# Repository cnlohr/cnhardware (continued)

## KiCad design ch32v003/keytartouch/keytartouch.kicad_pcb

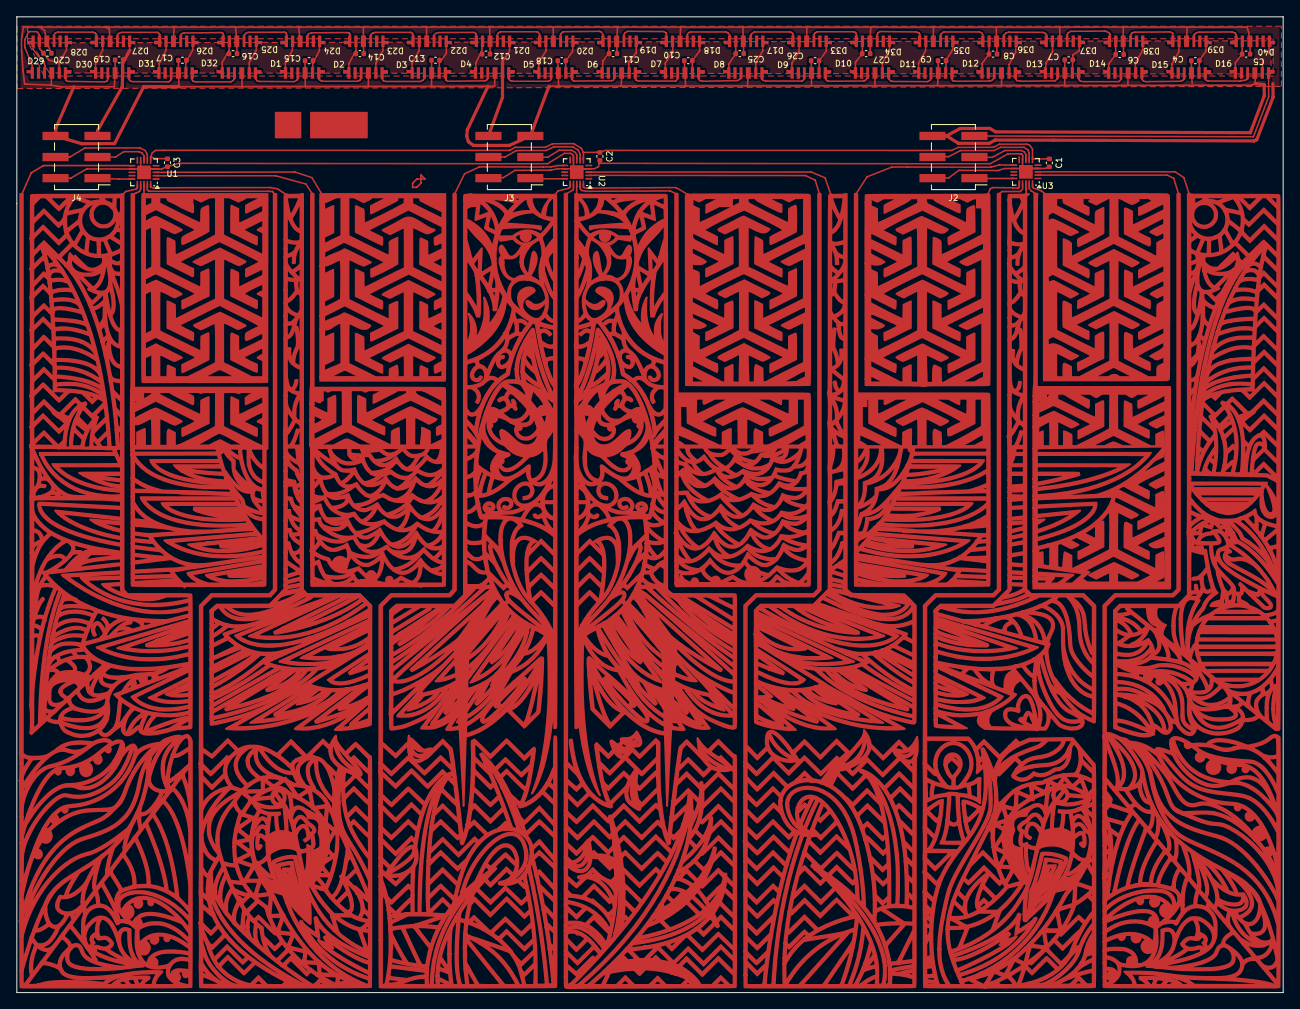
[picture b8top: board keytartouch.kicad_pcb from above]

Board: 2 copper layers, 152.5 x 117.5 mm, 70 parts (0 on the bottom side), 77 nets.

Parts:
C1, C2, C3, C4, C5, C6, C7, C8, C9, C10, C11, C12, C13, C14, C15, C16, C17, C18, C19, C20, C25, C26, C27: .1u; C_0402_1005Metric
D1, D2, D3, D4, D5, D6, D7, D8, D9, D10, D11, D12, D13, D14, D15, D16, D17, D18, D19, D20, D21, D22, D23, D24, D25, D26, D27, D28, D29, D30, D31, D32, D33, D34, D35, D36, D37, D38, D39, D40: SK6805SIDE-FRGBW-BW-P6
J1: CONNS; kelseytop
J2: CC; PinHeader_2x03_P2.54mm_Vertical_SMD
J3: CB; PinHeader_2x03_P2.54mm_Vertical_SMD
J4: CA; PinHeader_2x03_P2.54mm_Vertical_SMD
U1, U2, U3: CH32V003F4U6; QFN-20-1EP_3x3mm_P0.4mm_EP1.65x1.65mm

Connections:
GND: C1.2, C2.2, C3.2, J2.2, J3.2, J4.2, U1.4 (VSS), U1.9 (PC2/SCL/URTS/T1BKIN/AETR/T2CH2/T1ETR), U1.12 (PC5/SCK/T1ETR/T2CH1ETR/SCL/UCK/T1CH3), U1.21 (GND), U2.4 (VSS), U2.9 (PC2/SCL/URTS/T1BKIN/AETR/T2CH2/T1ETR), U2.12 (PC5/SCK/T1ETR/T2CH1ETR/SCL/UCK/T1CH3), U2.21 (GND), U3.4 (VSS), U3.9 (PC2/SCL/URTS/T1BKIN/AETR/T2CH2/T1ETR), U3.12 (PC5/SCK/T1ETR/T2CH1ETR/SCL/UCK/T1CH3), U3.21 (GND)
GND1: C4.2, C5.2, C6.2, C7.2, C8.2, C9.2, C10.2, C11.2, C12.2, C13.2, C14.2, C15.2, C16.2, C17.2, C18.2, C19.2, C20.2, C25.2, C26.2, C27.2, D1.4 (GND), D2.4 (GND), D3.4 (GND), D4.4 (GND), D5.4 (GND), D6.4 (GND), D7.4 (GND), D8.4 (GND), D9.4 (GND), D10.4 (GND), D11.4 (GND), D12.4 (GND), D13.4 (GND), D14.4 (GND), D15.4 (GND), D16.4 (GND), D17.4 (GND), D18.4 (GND), D19.4 (GND), D20.4 (GND), D21.4 (GND), D22.4 (GND), D23.4 (GND), D24.4 (GND), D25.4 (GND), D26.4 (GND), D27.4 (GND), D28.4 (GND), D29.4 (GND), D30.4 (GND), D31.4 (GND), D32.4 (GND), D33.4 (GND), D34.4 (GND), D35.4 (GND), D36.4 (GND), D37.4 (GND), D38.4 (GND), D39.4 (GND), D40.4 (GND), J2.6, J3.5, J4.6
unnamed: D1.6 (DIN), D2.3 (DOUT)
unnamed: D1.3 (DOUT), D32.6 (DIN)
unnamed: D2.6 (DIN), D3.3 (DOUT)
unnamed: D3.6 (DIN), D4.3 (DOUT)
unnamed: D4.6 (DIN), D5.3 (DOUT)
unnamed: D5.6 (DIN), D6.3 (DOUT)
unnamed: D6.6 (DIN), D7.3 (DOUT)
unnamed: D7.6 (DIN), D8.3 (DOUT)
unnamed: D8.6 (DIN), D9.3 (DOUT)
unnamed: D10.6 (DIN), D11.3 (DOUT)
unnamed: D9.6 (DIN), D10.3 (DOUT)
unnamed: D11.6 (DIN), D12.3 (DOUT)
unnamed: D12.6 (DIN), D13.3 (DOUT)
unnamed: D13.6 (DIN), D14.3 (DOUT)
unnamed: D14.6 (DIN), D15.3 (DOUT)
unnamed: D15.6 (DIN), D16.3 (DOUT)
unnamed: D17.6 (DIN), D18.3 (DOUT)
unnamed: D17.3 (DOUT), D33.6 (DIN)
unnamed: D18.6 (DIN), D19.3 (DOUT)
unnamed: D19.6 (DIN), D20.3 (DOUT)
unnamed: D20.6 (DIN), D21.3 (DOUT)
unnamed: D21.6 (DIN), D22.3 (DOUT)
unnamed: D22.6 (DIN), D23.3 (DOUT)
unnamed: D23.6 (DIN), D24.3 (DOUT)
unnamed: D24.6 (DIN), D25.3 (DOUT)
unnamed: D25.6 (DIN), D26.3 (DOUT)
unnamed: D26.6 (DIN), D27.3 (DOUT)
unnamed: D27.6 (DIN), D28.3 (DOUT)
unnamed: D28.6 (DIN), D29.3 (DOUT)
unnamed: D29.6 (DIN), D30.3 (DOUT)
unnamed: D30.6 (DIN), D31.3 (DOUT)
unnamed: D31.6 (DIN), D32.3 (DOUT)
unnamed: D33.3 (DOUT), D34.6 (DIN)
unnamed: D34.3 (DOUT), D35.6 (DIN)
unnamed: D35.3 (DOUT), D36.6 (DIN)
unnamed: D36.3 (DOUT), D37.6 (DIN)
unnamed: D37.3 (DOUT), D38.6 (DIN)
unnamed: D38.3 (DOUT), D39.6 (DIN)
unnamed: D39.3 (DOUT), D40.6 (DIN)
unnamed: J2.1, U3.15 (PD1/SWIO/AETR/T1CH3/SCL/URX)
unnamed: J2.3, U3.8 (PC1/SDA/NSS/T2CH4/T2CH1ETR/T1BKIN/URX)
unnamed: J2.4, U3.7 (PC0/T2CH3/UTX/NSS/T1CH3)
unnamed: J3.1, U2.15 (PD1/SWIO/AETR/T1CH3/SCL/URX)
unnamed: J3.3, U2.8 (PC1/SDA/NSS/T2CH4/T2CH1ETR/T1BKIN/URX)
unnamed: J3.4, U2.7 (PC0/T2CH3/UTX/NSS/T1CH3)
unnamed: J4.1, U1.15 (PD1/SWIO/AETR/T1CH3/SCL/URX)
unnamed: J4.3, U1.8 (PC1/SDA/NSS/T2CH4/T2CH1ETR/T1BKIN/URX)
unnamed: J4.4, U1.7 (PC0/T2CH3/UTX/NSS/T1CH3)
T00: J1.8, U1.3 (PA2/OSCO/A0/T1CH2N/OPP0/AETR2)
T01: J1.7, U1.2 (PA1/OSCI/A1/T1CH2/OPN0)
T02: J1.1, U1.11 (PC4/A2/T1CH4/MCO/T1CH1CH2N)
T03: J1.2, U1.16 (PD2/A3/T1CH1/T2CH3/T1CH2N)
T04: J1.3, U1.17 (PD3/A4/T2CH2/AETR/UCTS/T1CH4)
T05: J1.5, U1.19 (PD5/A5/UTX/T2CH4/URX)
T06: J1.4, U1.18 (PD4/A7/UCK/T2CH1ETR/OPO/T1CH4ETR)
T07: J1.6, U1.20 (PD6/A7/URX/T2CH3/UTX)
T10: J1.16, U2.3 (PA2/OSCO/A0/T1CH2N/OPP0/AETR2)
T11: J1.15, U2.2 (PA1/OSCI/A1/T1CH2/OPN0)
T12: J1.9, U2.11 (PC4/A2/T1CH4/MCO/T1CH1CH2N)
T13: J1.10, U2.16 (PD2/A3/T1CH1/T2CH3/T1CH2N)
T14: J1.11, U2.17 (PD3/A4/T2CH2/AETR/UCTS/T1CH4)
T15: J1.13, U2.19 (PD5/A5/UTX/T2CH4/URX)
T16: J1.12, U2.18 (PD4/A7/UCK/T2CH1ETR/OPO/T1CH4ETR)
T17: J1.14, U2.20 (PD6/A7/URX/T2CH3/UTX)
T20: J1.24, U3.3 (PA2/OSCO/A0/T1CH2N/OPP0/AETR2)
T21: J1.23, U3.2 (PA1/OSCI/A1/T1CH2/OPN0)
T22: J1.17, U3.11 (PC4/A2/T1CH4/MCO/T1CH1CH2N)
T23: J1.18, U3.16 (PD2/A3/T1CH1/T2CH3/T1CH2N)
T24: J1.19, U3.17 (PD3/A4/T2CH2/AETR/UCTS/T1CH4)
T25: J1.21, U3.19 (PD5/A5/UTX/T2CH4/URX)
T26: J1.20, U3.18 (PD4/A7/UCK/T2CH1ETR/OPO/T1CH4ETR)
T27: J1.22, U3.20 (PD6/A7/URX/T2CH3/UTX)
VAA: C4.1, C5.1, C6.1, C7.1, C8.1, C9.1, C10.1, C11.1, C12.1, C13.1, C14.1, C15.1, C16.1, C17.1, C18.1, C19.1, C20.1, C25.1, C26.1, C27.1, D1.1 (W-VDD), D1.5 (VDD), D2.1 (W-VDD), D2.5 (VDD), D3.1 (W-VDD), D3.5 (VDD), D4.1 (W-VDD), D4.5 (VDD), D5.1 (W-VDD), D5.5 (VDD), D6.1 (W-VDD), D6.5 (VDD), D7.1 (W-VDD), D7.5 (VDD), D8.1 (W-VDD), D8.5 (VDD), D9.1 (W-VDD), D9.5 (VDD), D10.1 (W-VDD), D10.5 (VDD), D11.1 (W-VDD), D11.5 (VDD), D12.1 (W-VDD), D12.5 (VDD), D13.1 (W-VDD), D13.5 (VDD), D14.1 (W-VDD), D14.5 (VDD), D15.1 (W-VDD), D15.5 (VDD), D16.1 (W-VDD), D16.5 (VDD), D17.1 (W-VDD), D17.5 (VDD), D18.1 (W-VDD), D18.5 (VDD), D19.1 (W-VDD), D19.5 (VDD), D20.1 (W-VDD), D20.5 (VDD), D21.1 (W-VDD), D21.5 (VDD), D22.1 (W-VDD), D22.5 (VDD), D23.1 (W-VDD), D23.5 (VDD), D24.1 (W-VDD), D24.5 (VDD), D25.1 (W-VDD), D25.5 (VDD), D26.1 (W-VDD), D26.5 (VDD), D27.1 (W-VDD), D27.5 (VDD), D28.1 (W-VDD), D28.5 (VDD), D29.1 (W-VDD), D29.5 (VDD), D30.1 (W-VDD), D30.5 (VDD), D31.1 (W-VDD), D31.5 (VDD), D32.1 (W-VDD), D32.5 (VDD), D33.1 (W-VDD), D33.5 (VDD), D34.1 (W-VDD), D34.5 (VDD), D35.1 (W-VDD), D35.5 (VDD), D36.1 (W-VDD), D36.5 (VDD), D37.1 (W-VDD), D37.5 (VDD), D38.1 (W-VDD), D38.5 (VDD), D39.1 (W-VDD), D39.5 (VDD), D40.1 (W-VDD), D40.5 (VDD), J3.6, J4.5
VDD: C1.1, C2.1, C3.1, U1.6 (VDD), U2.6 (VDD), U3.6 (VDD)
WSIN: D16.6 (DIN), J2.5

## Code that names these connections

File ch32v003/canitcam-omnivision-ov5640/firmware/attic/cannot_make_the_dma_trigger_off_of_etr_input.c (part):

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#include <stdio.h>

// Connections
//  PA1 = XCLK <<<< Test
//  PD0 = SCL
//  PD3 = SDA
//  PD4 = PCLK <<<< Test
//  PD2 = VSYNC

#define PIN_XCK   PD6
#define PIN_SCL   PD0
#define PIN_SDA   PD3
#define PIN_PCK   PD4
#define PIN_VS    PD2
#define PIN_HS    PD5 // Maybe not needed?
#define PIN_RST   PD7

#define DELAY1 Delay_Us(1);
#define DELAY2 Delay_Us(2);
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
	// TIM1_TRIG/TIM1_COM/TIM1_CH4 -> DMA1_Channel4

	// Remap, so PD4 is input for ETR
	AFIO->PCFR1 |=AFIO_PCFR1_TIM1_REMAP_1;

	funPinMode( PIN_PCK,   GPIO_CFGLR_IN_FLOAT );
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	TIM1->CTLR1 |= TIM_CEN; // Enable
	TIM1->CNT = 0;

	// TIM2 full remap, to get output on PD6
	AFIO->PCFR1 |= AFIO_PCFR1_TIM2_REMAP;
	funPinMode( PIN_XCK,   GPIO_CFGLR_OUT_50Mhz_AF_PP );
	TIM2->PSC = 0x0000;      // Prescaler 
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
	ConfigureCamera();

	while( funDigitalRead( PD5 ) == 0 );// printf( "%02x", GPIOC->INDR );
	while( funDigitalRead( PD5 ) == 1 );// printf( "%02x", GPIOC->INDR );
//	while( funDigitalRead( PD5 ) == 0 ) printf( "%02x", GPIOC->INDR );
//	while( funDigitalRead( PD5 ) == 0 );
//	while( funDigitalRead( PD5 ) == 1 );
	DMA1_Channel4->CFGR = 0; // Disable DMA.

	printf( "Remain:%d/%d/%d/%d/%d/%d/%d / %d\n", 
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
